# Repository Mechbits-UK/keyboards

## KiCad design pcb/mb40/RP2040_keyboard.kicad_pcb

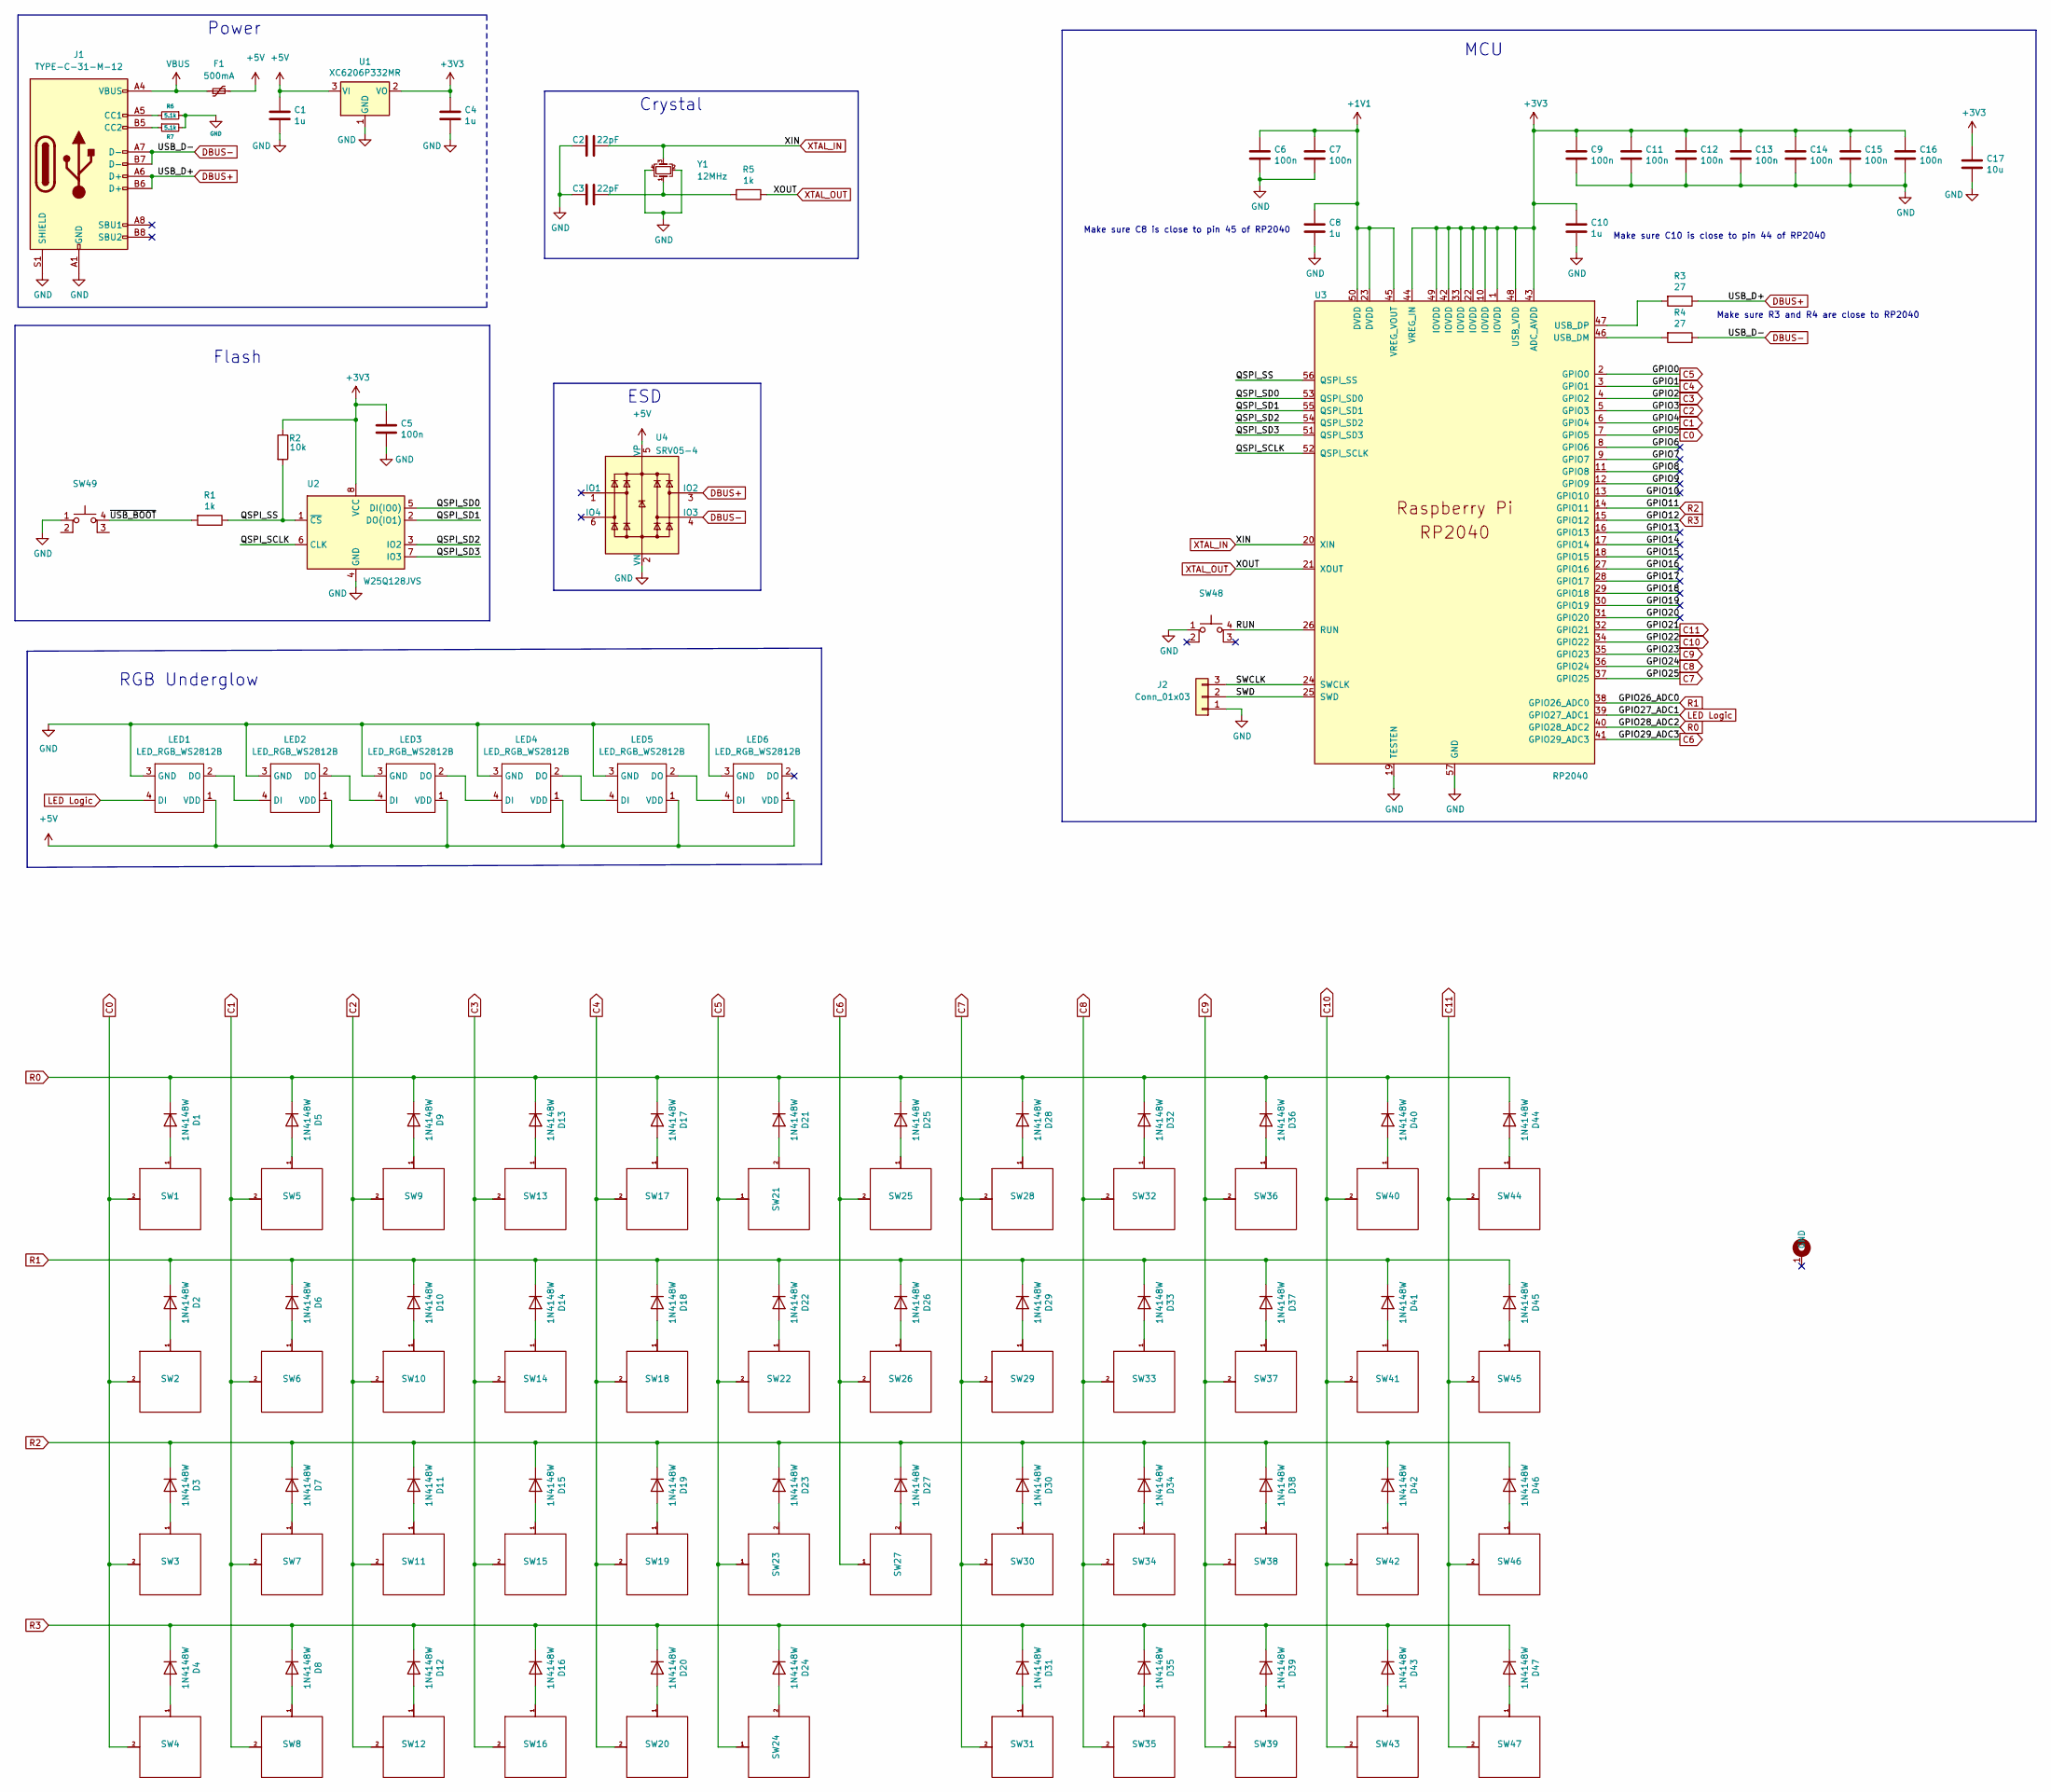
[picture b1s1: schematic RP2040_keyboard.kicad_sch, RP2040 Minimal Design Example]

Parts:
C1, C4, C8, C10: 1u; C_0402_1005Metric; LCSC C52923
C2, C3: 22pF; C_0402_1005Metric; LCSC C1555
C5, C6, C7, C9, C11, C12, C13, C14, C15, C16: 100n; C_0402_1005Metric; LCSC C1525
C17: 10u; C_0402_1005Metric; LCSC C15525
D1, D2, D3, D4, D5, D6, D7, D8, D9, D10, D11, D12, D13, D14, D15, D16, D17, D18, D19, D20, D21, D22, D23, D24, D25, D26, D27, D28, D29, D30, D31, D32, D33, D34, D35, D36, D37, D38, D39, D40, D41, D42, D43, D44, D45, D46, D47: 1N4148W; D_SOD-123; Manufacturer Part Number 1N4148W; LCSC C81598
F1: 500mA; Fuse_1206_3216Metric; LCSC C70076
H1: MountingHole-KB40; 40_pcb_mounting_holes
J1: TYPE-C-31-M-12; USB_C_Receptacle_Hroparts_TYPE-C-31-M-12; LCSC C165948
J2: Conn_01x03; PinHeader_1x03_P2.54mm_Vertical
LED1, LED2, LED3, LED4, LED5, LED6: LED_RGB_WS2812B; LED_WS2812B_PLCC4_5.0x5.0mm_P3.2mm; LCSC C2761795
R1, R5: 1k; C_0402_1005Metric; LCSC C11702
R2: 10k; C_0402_1005Metric; LCSC C25741
R3, R4: 27; C_0603_1608Metric; LCSC C25190
R6, R7: 5.1k; R_0402_1005Metric; Manufacturer Part Number 0402WGF5101TCE; LCSC C25905
SW1, SW2, SW3, SW4, SW5, SW6, SW7, SW8, SW9, SW10, SW11, SW12, SW13, SW14, SW15, SW16, SW17, SW18, SW19, SW20, SW21, SW22, SW23, SW25, SW26, SW27, SW28, SW29, SW30, SW31, SW32, SW33, SW34, SW35, SW36, SW37, SW38, SW39, SW40, SW41, SW42, SW43, SW44, SW45, SW46, SW47: MX Switch; MX100H-alt; LCSC C2803348
SW24: MX Switch; MX200H-alt; LCSC C2803348
SW48, SW49: SW_MEC_5E; SMD-SW-4_5.1x5.1x1.5; LCSC C318884
U1: XC6206P332MR; SOT-23; LCSC C5446
U2: W25Q128JVS; SOIC-8_5.23x5.23mm_P1.27mm; LCSC C97521
U3: RP2040; RP2040-QFN-56; LCSC C2040
U4: SRV05-4; SOT-23-6; LCSC C85364
Y1: 12MHz; Crystal_SMD_3225-4Pin_3.2x2.5mm; LCSC C9002

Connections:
+1V1: C6.1, C7.1, C8.1, U3.23 (DVDD), U3.45 (VREG_VOUT), U3.50 (DVDD)
+3V3: C4.1, C5.1, C9.1, C10.1, C11.1, C12.1, C13.1, C14.1, C15.1, C16.1, C17.1, R2.1, U1.2 (VO), U2.8 (VCC), U3.1 (IOVDD), U3.10 (IOVDD), U3.22 (IOVDD), U3.33 (IOVDD), U3.42 (IOVDD), U3.43 (ADC_AVDD), U3.44 (VREG_IN), U3.48 (USB_VDD), U3.49 (IOVDD)
+5V: C1.1, F1.2, LED1.1 (VDD), LED2.1 (VDD), LED3.1 (VDD), LED4.1 (VDD), LED5.1 (VDD), LED6.1 (VDD), U1.3 (VI), U4.5 (VP)
/GPIO6: U3.8 (GPIO6)
/GPIO7: U3.9 (GPIO7)
/GPIO8: U3.11 (GPIO8)
/GPIO9: U3.12 (GPIO9)
/GPIO10: U3.13 (GPIO10)
/GPIO13: U3.16 (GPIO13)
/GPIO14: U3.17 (GPIO14)
/GPIO15: U3.18 (GPIO15)
/GPIO16: U3.27 (GPIO16)
/GPIO17: U3.28 (GPIO17)
/GPIO18: U3.29 (GPIO18)
/GPIO19: U3.30 (GPIO19)
/GPIO20: U3.31 (GPIO20)
/QSPI_SCLK: U2.6 (CLK), U3.52 (QSPI_SCLK)
/QSPI_SD0: U2.5 (DI(IO0)), U3.53 (QSPI_SD0)
/QSPI_SD1: U2.2 (DO(IO1)), U3.55 (QSPI_SD1)
/QSPI_SD2: U2.3 (IO2), U3.54 (QSPI_SD2)
/QSPI_SD3: U2.7 (IO3), U3.51 (QSPI_SD3)
/QSPI_SS: R1.1, R2.2, U2.1 (~CS), U3.56 (QSPI_SS)
/RUN: SW48.4 (A), U3.26 (RUN)
/SWCLK: J2.3, U3.24 (SWCLK)
/SWD: J2.2, U3.25 (SWD)
/~USB_BOOT: R1.2, SW49.4 (A)
C0: SW1.2, SW2.2, SW3.2, SW4.2, U3.7 (GPIO5)
C1: SW5.2, SW6.2, SW7.2, SW8.2, U3.6 (GPIO4)
C2: SW9.2, SW10.2, SW11.2, SW12.2, U3.5 (GPIO3)
C3: SW13.2, SW14.2, SW15.2, SW16.2, U3.4 (GPIO2)
C4: SW17.2, SW18.2, SW19.2, SW20.2, U3.3 (GPIO1)
C5: SW21.1, SW22.2, SW23.1, SW24.1, U3.2 (GPIO0)
C6: SW25.2, SW26.2, SW27.1, U3.41 (GPIO29_ADC3)
C7: SW28.2, SW29.2, SW30.2, SW31.2, U3.37 (GPIO25)
C8: SW32.2, SW33.2, SW34.2, SW35.2, U3.36 (GPIO24)
C9: SW36.2, SW37.2, SW38.2, SW39.2, U3.35 (GPIO23)
C10: SW40.2, SW41.2, SW42.2, SW43.2, U3.34 (GPIO22)
C11: SW44.2, SW45.2, SW46.2, SW47.2, U3.32 (GPIO21)
DBUS+: J1.A6 (D+), J1.B6 (D+), R3.1, U4.3 (IO2)
DBUS-: J1.A7 (D-), J1.B7 (D-), R4.1, U4.4 (IO3)
GND: C1.2, C2.2, C3.2, C4.2, C5.2, C6.2, C7.2, C8.2, C9.2, C10.2, C11.2, C12.2, C13.2, C14.2, C15.2, C16.2, C17.2, J1.A1 (GND), J1.B1 (GND), J1.S1 (SHIELD), J2.1, LED1.3 (GND), LED2.3 (GND), LED3.3 (GND), LED4.3 (GND), LED5.3 (GND), LED6.3 (GND), R6.1, R7.2, SW48.1, SW49.1, U1.1 (GND), U2.4 (GND), U3.19 (TESTEN), U3.57 (GND), U4.2 (VN), Y1.2, Y1.4
LED Logic: LED1.4 (DI), U3.39 (GPIO27_ADC1)
unnamed: C3.1, R5.2, Y1.1
unnamed: D1.2 (A), SW1.1
unnamed: D2.2 (A), SW2.1
unnamed: D3.2 (A), SW3.1
unnamed: D4.2 (A), SW4.1
unnamed: D5.2 (A), SW5.1
unnamed: D6.2 (A), SW6.1
unnamed: D7.2 (A), SW7.1
unnamed: D8.2 (A), SW8.1
unnamed: D9.2 (A), SW9.1
unnamed: D10.2 (A), SW10.1
unnamed: D11.2 (A), SW11.1
unnamed: D12.2 (A), SW12.1
unnamed: D13.2 (A), SW13.1
unnamed: D14.2 (A), SW14.1
unnamed: D15.2 (A), SW15.1
unnamed: D16.2 (A), SW16.1
unnamed: D17.2 (A), SW17.1
unnamed: D18.2 (A), SW18.1
unnamed: D19.2 (A), SW19.1
unnamed: D20.2 (A), SW20.1
unnamed: D21.2 (A), SW21.2
unnamed: D22.2 (A), SW22.1
unnamed: D23.2 (A), SW23.2
unnamed: D24.2 (A), SW24.2
unnamed: D25.2 (A), SW25.1
unnamed: D26.2 (A), SW26.1
unnamed: D27.2 (A), SW27.2
unnamed: D28.2 (A), SW28.1
unnamed: D29.2 (A), SW29.1
unnamed: D30.2 (A), SW30.1
unnamed: D31.2 (A), SW31.1
unnamed: D32.2 (A), SW32.1
unnamed: D33.2 (A), SW33.1
unnamed: D34.2 (A), SW34.1
unnamed: D35.2 (A), SW35.1
unnamed: D36.2 (A), SW36.1
unnamed: D37.2 (A), SW37.1
unnamed: D38.2 (A), SW38.1
unnamed: D39.2 (A), SW39.1
unnamed: D40.2 (A), SW40.1
unnamed: D41.2 (A), SW41.1
unnamed: D42.2 (A), SW42.1
unnamed: D43.2 (A), SW43.1
unnamed: D44.2 (A), SW44.1
unnamed: D45.2 (A), SW45.1
unnamed: D46.2 (A), SW46.1
unnamed: D47.2 (A), SW47.1
unnamed: J1.A5 (CC1), R6.2
unnamed: J1.B5 (CC2), R7.1
unnamed: LED1.2 (DO), LED2.4 (DI)
unnamed: LED2.2 (DO), LED3.4 (DI)
unnamed: LED3.2 (DO), LED4.4 (DI)
unnamed: LED4.2 (DO), LED5.4 (DI)
unnamed: LED5.2 (DO), LED6.4 (DI)
unnamed: R3.2, U3.47 (USB_DP)
unnamed: R4.2, U3.46 (USB_DM)
R0: D1.1 (K), D5.1 (K), D9.1 (K), D13.1 (K), D17.1 (K), D21.1 (K), D25.1 (K), D28.1 (K), D32.1 (K), D36.1 (K), D40.1 (K), D44.1 (K), U3.40 (GPIO28_ADC2)
R1: D2.1 (K), D6.1 (K), D10.1 (K), D14.1 (K), D18.1 (K), D22.1 (K), D26.1 (K), D29.1 (K), D33.1 (K), D37.1 (K), D41.1 (K), D45.1 (K), U3.38 (GPIO26_ADC0)
R2: D3.1 (K), D7.1 (K), D11.1 (K), D15.1 (K), D19.1 (K), D23.1 (K), D27.1 (K), D30.1 (K), D34.1 (K), D38.1 (K), D42.1 (K), D46.1 (K), U3.14 (GPIO11)
R3: D4.1 (K), D8.1 (K), D12.1 (K), D16.1 (K), D20.1 (K), D24.1 (K), D31.1 (K), D35.1 (K), D39.1 (K), D43.1 (K), D47.1 (K), U3.15 (GPIO12)
VBUS: F1.1, J1.A4 (VBUS), J1.B4 (VBUS)
XTAL_IN: C2.1, U3.20 (XIN), Y1.3
XTAL_OUT: R5.1, U3.21 (XOUT)

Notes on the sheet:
Power
Make sure R3 and R4 are close to RP2040
RGB Underglow
ESD
Make sure C8 is close to pin 45 of RP2040
MCU
Crystal
Flash
Make sure C10 is close to pin 44 of RP2040

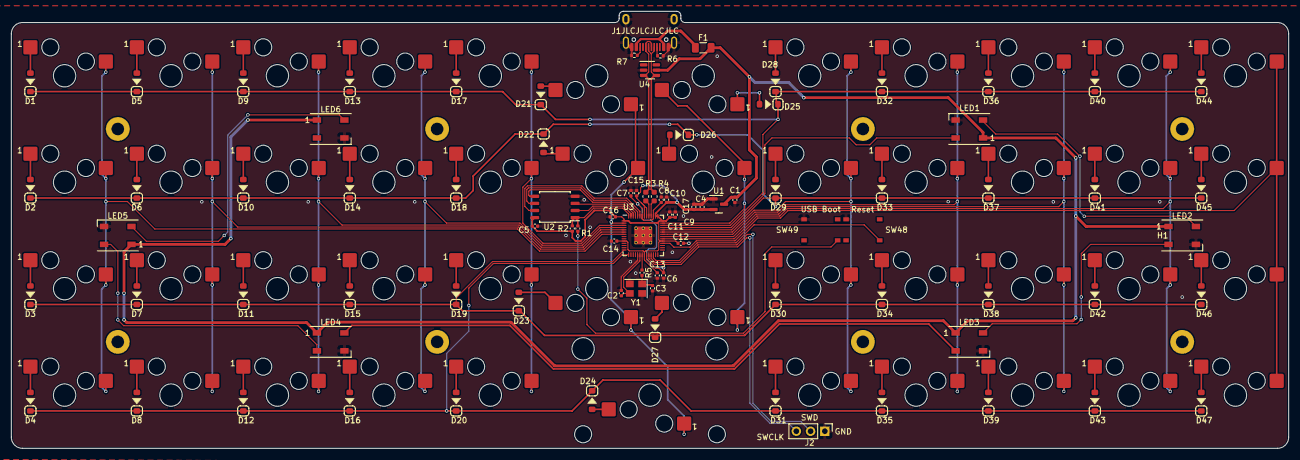
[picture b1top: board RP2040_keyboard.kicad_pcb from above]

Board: 2 copper layers, 228.0 x 78.0 mm, 135 parts (0 on the bottom side), 93 nets.

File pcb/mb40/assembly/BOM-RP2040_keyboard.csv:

Comment,Designator,Footprint,LCSC
1k,"R1,R5",C_0402_1005Metric,C11702
100n,"C11,C12,C13,C14,C15,C16,C5,C6,C7,C9",C_0402_1005Metric,C1525
10u,C17,C_0402_1005Metric,C15525
22pF,"C2,C3",C_0402_1005Metric,C1555
TYPE-C-31-M-12,J1,USB_C_Receptacle_Hroparts_TYPE-C-31-M-12,C165948
RP2040,U3,RP2040-QFN-56,C2040
27,"R3,R4",C_0603_1608Metric,C25190
10k,R2,C_0402_1005Metric,C25741
5.1k,"R6,R7",R_0402_1005Metric,C25905
LED_RGB_WS2812B,"LED1,LED2,LED3,LED4,LED5,LED6",LED_WS2812B_PLCC4_5.0x5.0mm_P3.2mm,C2761795
SW_MEC_5E,"SW48,SW49",SMD-SW-4_5.1x5.1x1.5,C318884
1u,"C1,C10,C4,C8",C_0402_1005Metric,C52923
XC6206P332MR,U1,SOT-23,C5446
500mA,F1,Fuse_1206_3216Metric,C70076
1N4148W,"D1,D10,D11,D12,D13,D14,D15,D16,D17,D18,D19,D2,D20,D21,D22,D23,D24,D25,D26,D27,D28,D29,D3,D30,D31,D32,D33,D34,D35,D36,D37,D38,D39,D4,D40,D41,D42,D43,D44,D45,D46,D47,D5,D6,D7,D8,D9",D_SOD-123,C81598
SRV05-4,U4,SOT-23-6,C85364
12MHz,Y1,Crystal_SMD_3225-4Pin_3.2x2.5mm,C9002
W25Q128JVS,U2,SOIC-8_5.23x5.23mm_P1.27mm,C97521

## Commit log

2022-09-19 Update rules.mk
    Enable tap dance support - https://docs.qmk.fm/#/feature_tap_dance
2022-09-19 Rename Images/Logo/mechbits_layout.svg to images/logo/mechbits_layout.svg
2022-09-24 Change LAYER_ back to _LAYER
2022-09-24 Add Tap Dance - Shift to Caps Lock
2022-09-24 Edit _LAYER
2022-09-24 Updated default layout, added tap dance support
    Updated default layout, added tap dance support to default and biggz layouts
2022-09-24 Add TD(TD_SHIFT_CAPS) to _LAYER4
2022-09-24 Updated Biggz keymap
2022-09-24 Added extra info
2022-09-24 Tidy biggz\keymap.c
